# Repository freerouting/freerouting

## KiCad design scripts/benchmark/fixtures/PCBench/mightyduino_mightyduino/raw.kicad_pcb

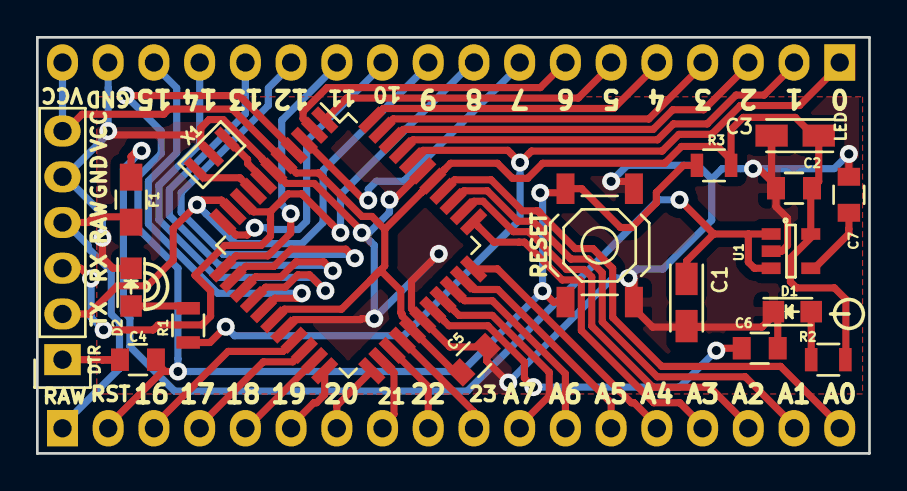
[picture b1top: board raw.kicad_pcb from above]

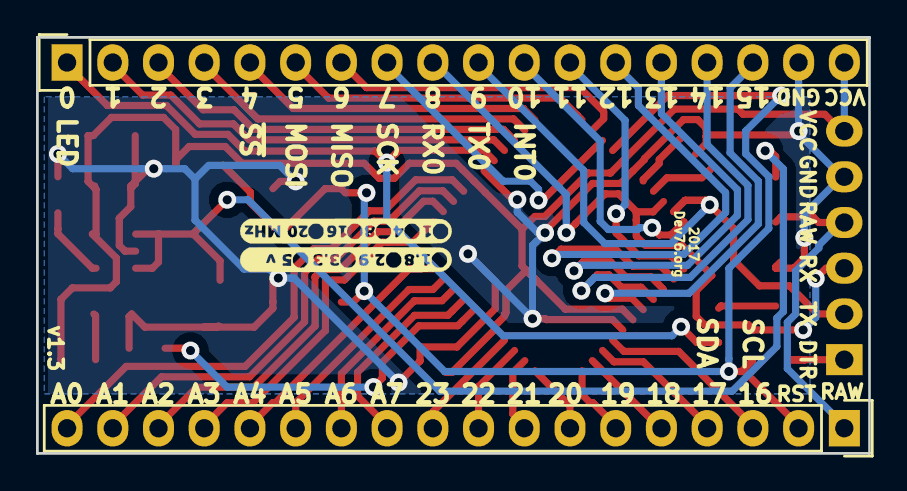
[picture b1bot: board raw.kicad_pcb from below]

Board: 2 copper layers, 46.2 x 23.1 mm, 20 parts (2 on the bottom side), 44 nets.

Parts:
C1, C3: 10u; TantalC_SizeA_EIA-3216_Reflow
C2, C4, C5, C6: 100n; C_0805
C7: 470p; C_0805
D1: red; LED_0805
D2: blue; LED_0805
F1: 500mA; C_0805_HandSoldering
IC1: ATMEGA644P-A; LQFP-44_10x10mm_Pitch0.8mm
P1, P3: CONN_01X18; Pin_Header_Straight_1x18
P2: CONN_01X06; Pin_Header_Straight_1x06
R1, R2: 330; R_0805
R3: 10k; R_0805
SW1: RESET; SW_SPST_TL3342
U1: MIC5219-3.3YM5; SOT-23-5
X1: CSTCE 16MHZ; CSTCEv2

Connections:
/A0: IC1.37, P3.18
/A1: IC1.36, P3.17
/A2: IC1.35, P3.16
/A3: IC1.34, P3.15
/A4: IC1.33, P3.14
/A5: IC1.32, P3.13
/A6: IC1.31, P3.12
/A7: IC1.30, P3.11
/D0: IC1.40, P1.1, R1.2
/D1: IC1.41, P1.2
/D2: IC1.42, P1.3
/D3: IC1.43, P1.4
/D4: IC1.44, P1.5
/D5: IC1.1, P1.6
/D6: IC1.2, P1.7
/D7: IC1.3, P1.8
/D8: IC1.9, P1.9, P2.3
/D9: IC1.10, P1.10, P2.2
/D10: IC1.11, P1.11
/D11: IC1.12, P1.12
/D12: IC1.13, P1.13
/D13: IC1.14, P1.14
/D14: IC1.15, P1.15
/D15: IC1.16, P1.16
/D16: IC1.19, P3.3
/D17: IC1.20, P3.4
/D18: IC1.21, P3.5
/D19: IC1.22, P3.6
/D20: IC1.23, P3.7
/D21: IC1.24, P3.8
/D22: IC1.25, P3.9
/D23: IC1.26, P3.10
/DTR: C4.2, P2.1
/RAW: F1.1, P2.4, P3.1
/RESET: C4.1, IC1.4, P3.2, R3.2, SW1.2
GND: C1.2, C2.2, C3.2, C5.2, C6.2, C7.2, D1.1, D2.1, IC1.6, IC1.18, IC1.28, IC1.39, P1.17, P2.5, SW1.1, U1.2, X1.3
unnamed: C1.1, F1.2, U1.1, U1.3
unnamed: C6.1, IC1.29
unnamed: C7.1, U1.4
unnamed: D1.2, R2.1
unnamed: D2.2, R1.1
unnamed: IC1.7, X1.1
unnamed: IC1.8, X1.2
VCC: C2.1, C3.1, C5.1, IC1.5, IC1.17, IC1.27, IC1.38, P1.18, P2.6, R2.2, R3.1, U1.5

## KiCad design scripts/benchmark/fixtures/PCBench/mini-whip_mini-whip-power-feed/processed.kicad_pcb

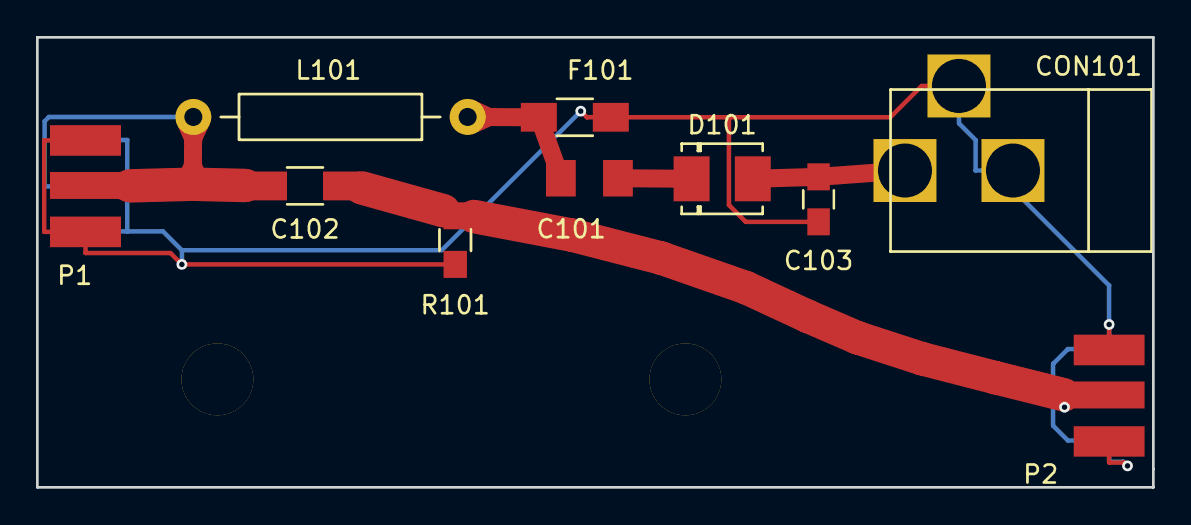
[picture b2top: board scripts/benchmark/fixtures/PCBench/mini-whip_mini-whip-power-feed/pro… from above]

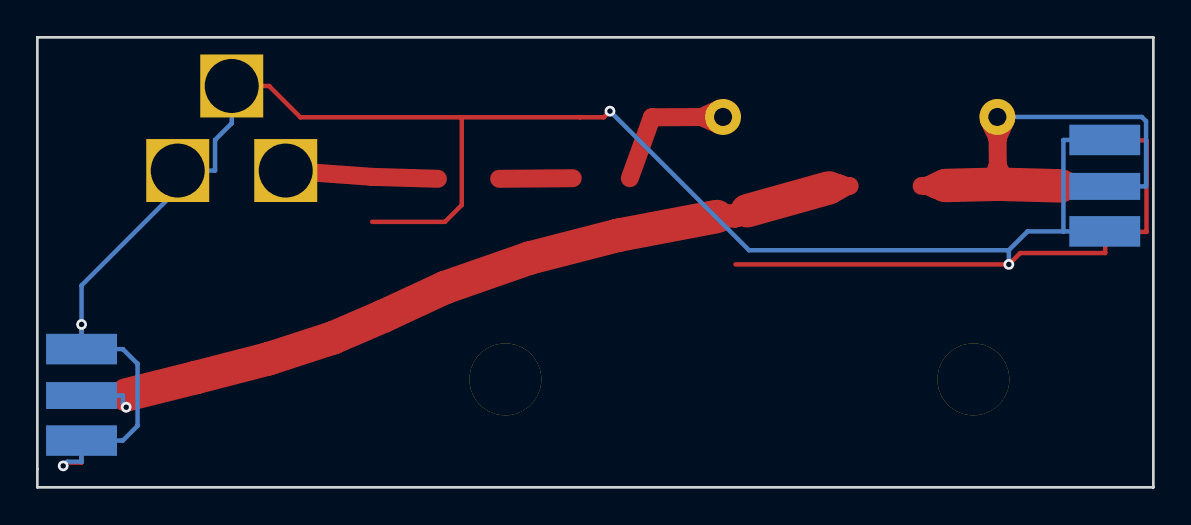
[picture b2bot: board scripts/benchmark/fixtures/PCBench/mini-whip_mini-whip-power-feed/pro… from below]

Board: 2 copper layers, 62.0 x 25.0 mm, 14 parts (2 on the bottom side), 6 nets.

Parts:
C101, C102: 1u; C_1206_HandSoldering
C103: 100n; C_0805_HandSoldering
CON101: BARREL_JACK
D101: FM5817; DO-214BA
F101: PTS120660V010; Fuse_SMD1206_Wave
H1, H2: MountingHole_4mm
L101: 470u; Choke_Horizontal_RM15mm
P1, P1_2, P2, P2_2: SMA-J
R101: 1k; R_0805_HandSoldering

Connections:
GND: C101.1, C103.1, CON101.2, CON101.3, P1.2, P1_2.2, P2.2, P2_2.2, R101.2
unnamed: C101.2, F101.1, L101.2
unnamed: C102.1, L101.1, P1.1, P1_2.1
unnamed: C102.2, P2.1, P2_2.1, R101.1
unnamed: C103.2, CON101.1, D101.2
unnamed: D101.1, F101.2

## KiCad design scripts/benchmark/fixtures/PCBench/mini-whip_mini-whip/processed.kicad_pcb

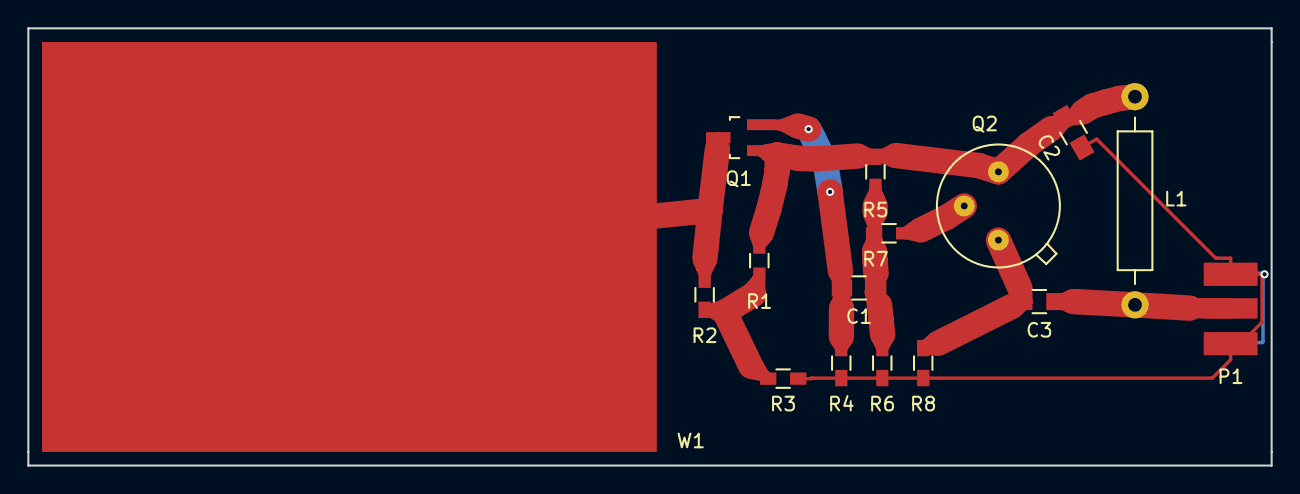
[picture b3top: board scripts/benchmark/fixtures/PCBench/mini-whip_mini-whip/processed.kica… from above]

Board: 2 copper layers, 91.0 x 32.0 mm, 17 parts (1 on the bottom side), 9 nets.

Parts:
C1, C2, C3: 560n; C_0805_HandSoldering
L1: 470 uH; Choke_Horizontal_RM15mm
P1, P1_2: SMA-J
Q1: MMBFJ310; SOT-23_Handsoldering
Q2: 2N5109; M246
R1, R2, R3: 1M; R_0603_HandSoldering
R4: 680; R_0603_HandSoldering
R5: 2k2; R_0603_HandSoldering
R6: 10k; R_0603_HandSoldering
R7: 47; R_0603_HandSoldering
R8: 220; R_0603_HandSoldering
W1: MINIWHIP

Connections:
Earth: C2.1, P1.2, P1_2.2, R3.2, R4.2, R6.2, R8.2
unnamed: C1.1, R5.2, R6.1, R7.2
unnamed: C1.2, Q1.2, R4.1
unnamed: C2.2, L1.1, Q1.1, Q2.3, R1.1, R5.1
unnamed: C3.1, L1.2, P1.1, P1_2.1
unnamed: C3.2, Q2.1, R8.1
unnamed: Q1.3, R2.1, W1.1
unnamed: Q2.2, R7.1
unnamed: R1.2, R2.2, R3.1
